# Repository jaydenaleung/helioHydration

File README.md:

# Helio Hydration - 3-Stage SODIS-Enhancing Water Bottle
Three-stage solar water disinfection (SODIS)-enhancing low-cost water bottle for NGO distribution to underserved and impoverished areas globally.

## Overview

This is a custom-designed water bottle to enhance solar water disinfection, a process where people utilize the sun's UV rays to kill bacteria in contaminated water, especially in places without access to clean water. The goal of this project is to design an efficient device that NGOs can buy and distribute to crisis areas around the world. The three stages are fiber membrane filtration, SODIS enhancement via clearer plastic materials, reflection, and heat-trapping, and indication/readiness tracking.

**Total time spent: 25.5 hours**

## Why I Created This Project

This project was created with a team for the Conrad Challenge: Water Challenge (though we decided not to submit it in the end). However, all the work for this Blueprint project was entirely my own - the team helped with other areas of the research and project. When brainstorming, we wanted to create a project that would have a 'wow' factor for Conrad Challenge judges, a real impact on the world and global issues, and a technically challenging aspect. After conducting much research around the field, we settled on this idea because we saw that SODIS relied too much on having perfectly sunny weather and non-turbid water. Indication was also an issue since people didn't know when it was truly disinfected.

## How It Works & Implementation

The mechanical structure is comprised of a body, a filter, and an indicator with its housing. The body is parabolic 100mm from the ground, and cylindrical until it reaches a height of ~227mm. Its largest diameter is 120mm. The filter mechanism is a clamp with a twist cap for the membrane fiber filter. The indicator uses the DS18B20 temperature sensor in conjunction with the GUVA-S12SD to calculate log reductions of E. coli.

Using the OneWire and DallasTemperature Arduino libraries, both the measured voltage from the UV photodiode sensor and the Celsius temperature from the temperature are gleaned. The following theoretical function calculates the number of log reductions at a specific time:

For the Arduino MCU, this function is used (using a discrete delta t):

I quite enjoyed applying the volume revolution and bacterial decay formulas I learned from AP Calculus BC this year. I've never really had a project where my class knowledge helped me so much. See the journal for more details.

## Bill of Materials (BOM)

| Name | Quantity | Price (per part) | Link |
| --- | --- | --- | --- |
| GUVA-S12SD UV Sensor Photodiode | 1   | $1.76 | https://www.aliexpress.us/item/3256806350705812.html |
| DS18B20 Temperature Sensor | 1   | $0.2328 | https://jlcpcb.com/partdetail/MSKSEMI-DS18B20MS/C5379069 |
| Ceramic Capacitor SMD | 2   | $0.0007 | https://jlcpcb.com/partdetail/1907-0402CG220J500NT/C1555 |
| Electrolytic Capacitor SMD | 2   | $0.0332 | https://jlcpcb.com/partdetail/14236-CL31A106KBHNNNE/C13585 |
| 4.7kΩ SMD Resistor | 1   | $0.0006 | https://jlcpcb.com/partdetail/26643-0402WGF4701TCE/C25900 |
| 10kΩ SMD Resistor | 1   | $0.001 | https://jlcpcb.com/partdetail/16079-0603WAJ0103T5E/C15401 |
| ATMEGA328P-PU Microcontroller | 1   | $2.2431 | https://jlcpcb.com/partdetail/MicrochipTech-ATMEGA328PPU/C33901 |
| LM7805-TO220 Voltage Regulator | 1   | $0.2084 | https://jlcpcb.com/partdetail/6334298-LM7805CT/C5444281 |
| Crystal Oscillator 16MHz | 1   | $0.1038 | https://jlcpcb.com/partdetail/TAITIENElec-XIHCELNANF16MHZ/C295075 |
| Probe Housing | 1   | $0.3170 | https://www.aliexpress.us/item/3256807782132862.html |
| Epoxy resin | ~1 mL | $0.01 | https://www.walmart.com/ip/Epoxy-Resin-1-Gallon-Kit-Art-Resin-for-DIY-Jewelry-Tabletops-Crystal-Clear-High-Performance-Resin-Epoxy/5478464246?wmlspartner=imp\_27795 |
| Membrane fiber filter | 1   | $0.29 | https://grupovoces.com/products/47mm-glass-fiber-filters-advantec-gc-90-100-pk-advantec |
| Clarified polypropylene (PP) | ~7.5 g | $0.0075 | Would need to contact a factory or ODM. Price taken from internet averages. |
| JLCPCB PCB | 1   | $1.06 ($7.45 with PCBA) | https://jlcpcb.com/ |
| **Total** |     |     | **$6.34**/bottle ($12.73 with PCBA) |

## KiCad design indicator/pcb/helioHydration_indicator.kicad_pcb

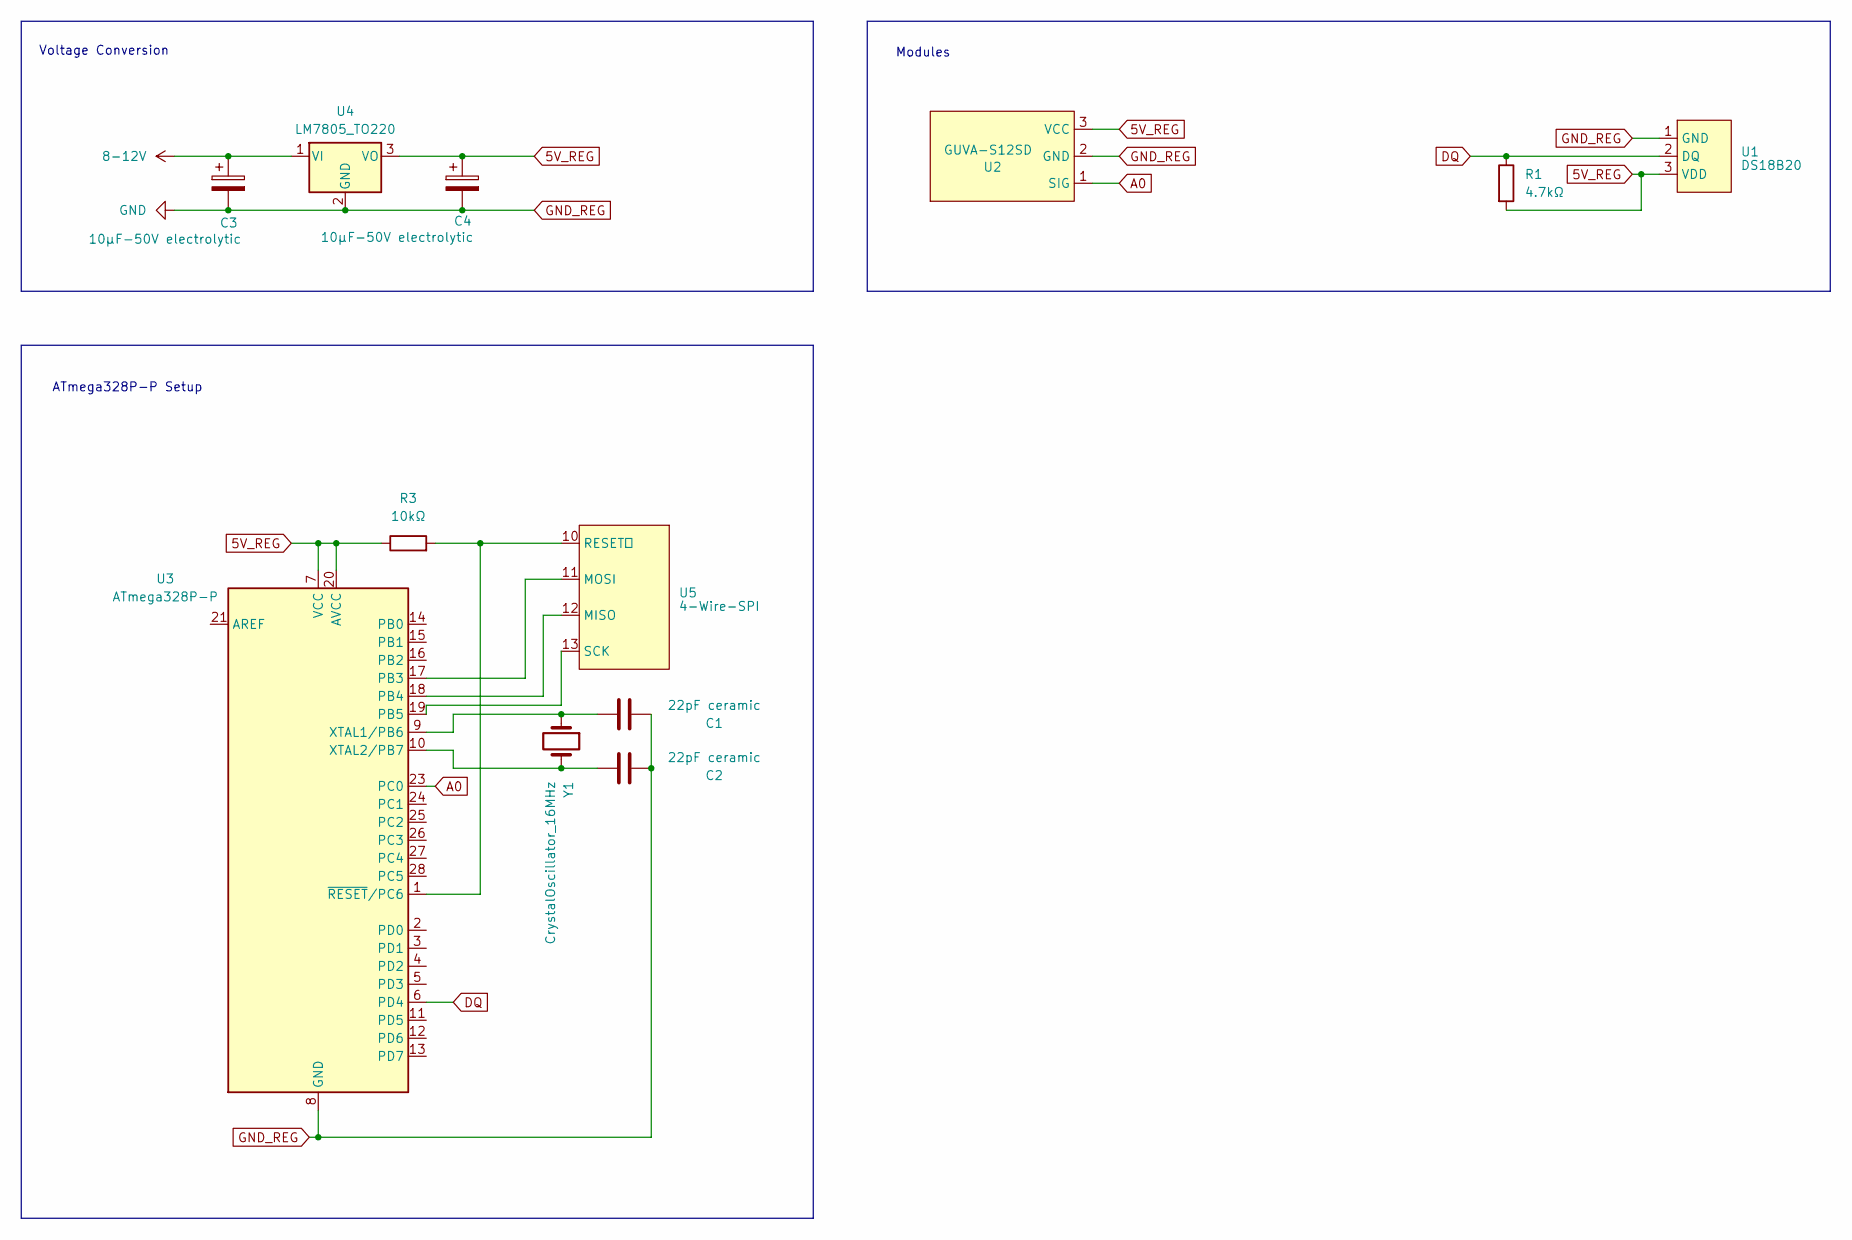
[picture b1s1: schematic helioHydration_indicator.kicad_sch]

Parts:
C1, C2: 22pF ceramic; C_0402_1005Metric
C3, C4: 10µF-50V electrolytic; C_1206_3216Metric
R1: 4.7kΩ; R_0402_1005Metric
R3: 10kΩ; R_0603_1608Metric
U1: DS18B20; DS18B20-MSKSEMI; Manufacturer Part .; LCSC Part Name .
U2: GUVA-S12SD; SZFYDOSH_11x27mm_Sensor
U3: ATmega328P-P; DIP-28_W7.62mm
U4: LM7805_TO220; TO-220-3_Vertical
U5: 4-Wire-SPI
Y1: CrystalOscillator_16MHz; Crystal_HC49-U_Vertical

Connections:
5V_REG: C4.1, R1.2, R3.1, U1.3 (VDD), U2.3 (VCC), U3.7 (VCC), U3.20 (AVCC), U4.3 (VO)
8-12V: C3.1, U4.1 (VI)
A0: U2.1 (SIG), U3.23 (PC0)
DQ: R1.1, U1.2 (DQ), U3.6 (PD4)
GND_REG: C1.1, C2.2, C3.2, C4.2, U1.1 (GND), U2.2 (GND), U3.8 (GND), U3.22 (GND), U4.2 (GND)
unnamed: U3.17 (PB3), U5.11 (MOSI)
unnamed: U3.18 (PB4), U5.12 (MISO)
unnamed: U3.19 (PB5), U5.13 (SCK)
unnamed: C1.2, U3.9 (XTAL1/PB6), Y1.1
unnamed: C2.1, U3.10 (XTAL2/PB7), Y1.2
unnamed: R3.2, U3.1 (~RESET/PC6), U5.10 (RESET)

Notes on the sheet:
ATmega328P-P Setup
Voltage Conversion
Modules

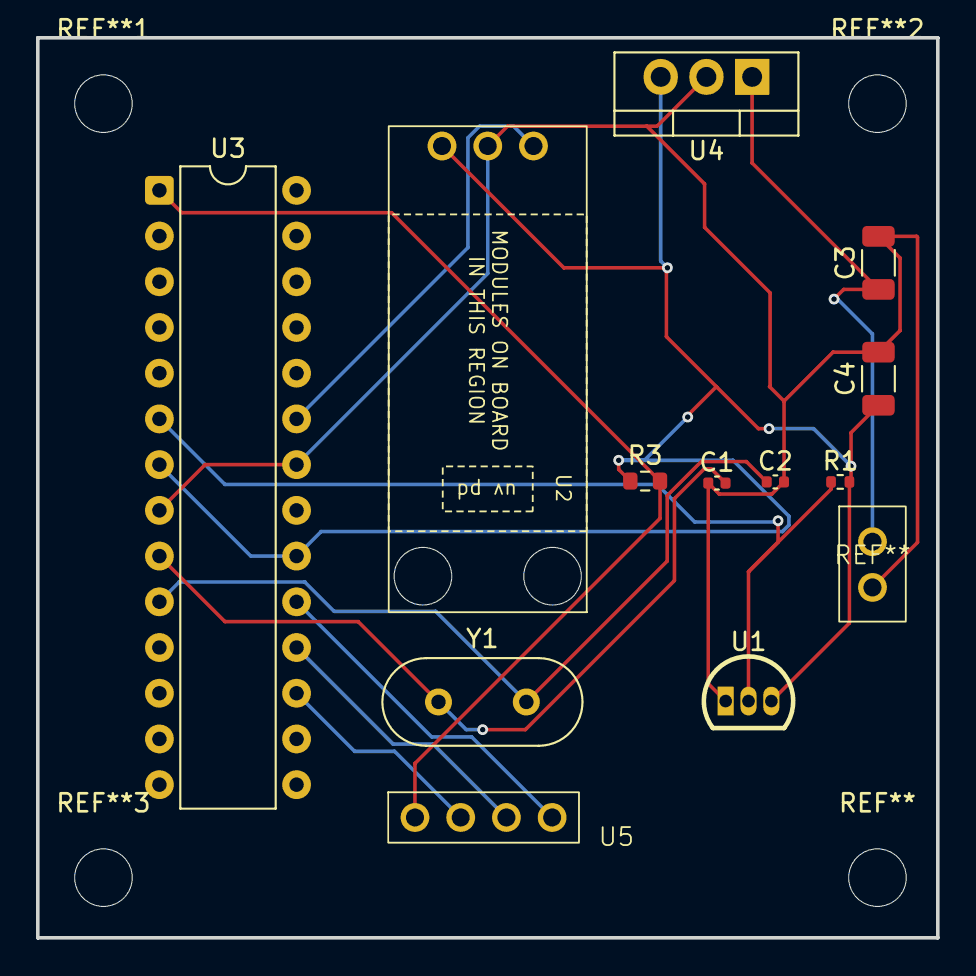
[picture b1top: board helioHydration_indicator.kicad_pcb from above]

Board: 2 copper layers, 50.0 x 50.0 mm, 12 parts (0 on the bottom side), 11 nets.

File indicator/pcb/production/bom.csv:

Designator,Footprint,Quantity,Value,LCSC Part #
"C1, C2",0402,2,22pF ceramic,
"C3, C4",1206,2,10µF-50V electrolytic,
R1,0402,1,4.7kΩ,
R3,0603,1,10kΩ,
U1,DS18B20-MSKSEMI,1,DS18B20,
U2,SZFYDOSH_11x27mm_Sensor,1,GUVA-S12SD,
U3,DIP-28_W7.62mm,1,ATmega328P-P,
U4,TO-220-3_Vertical,1,LM7805_TO220,
U5,4-Wire-SPI,1,4-Wire-SPI,
Y1,Crystal_HC49-U_Vertical,1,CrystalOscillator_16MHz,

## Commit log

2026-01-02 cad filter beta
2026-01-02 fix cap, upload step and stl files
2026-01-02 added render
2026-01-04 finish indicator pcb and schematic
2026-01-05 make indicator housing
2026-01-11 finishing touches and full assy
2026-01-11 add step
2026-01-12 update text
2026-01-12 Add images and improve project overview in README
    Updated README.md to include images and enhance project description.
2026-01-12 update pcb
2026-01-12 update gerbers organization
2026-01-12 updated bom
2026-01-12 update bom
2026-01-12 modified for 3d printing
2026-01-19 make adapter
2026-01-19 revert this
2026-01-19 Revert "revert this"
    This reverts commit 2f62f56bc3b80bfbb911c09e7c4823a3de9b39f3.
    revert commit
2026-01-19 fix housing top
